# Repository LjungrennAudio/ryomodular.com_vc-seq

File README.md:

# ryomodular.com_vc-seq
 yup - here he is, he's got his own repo! it's the vc-seq!

240901254

mostly just a repo to hold the documentation relating to this module by ro modular.

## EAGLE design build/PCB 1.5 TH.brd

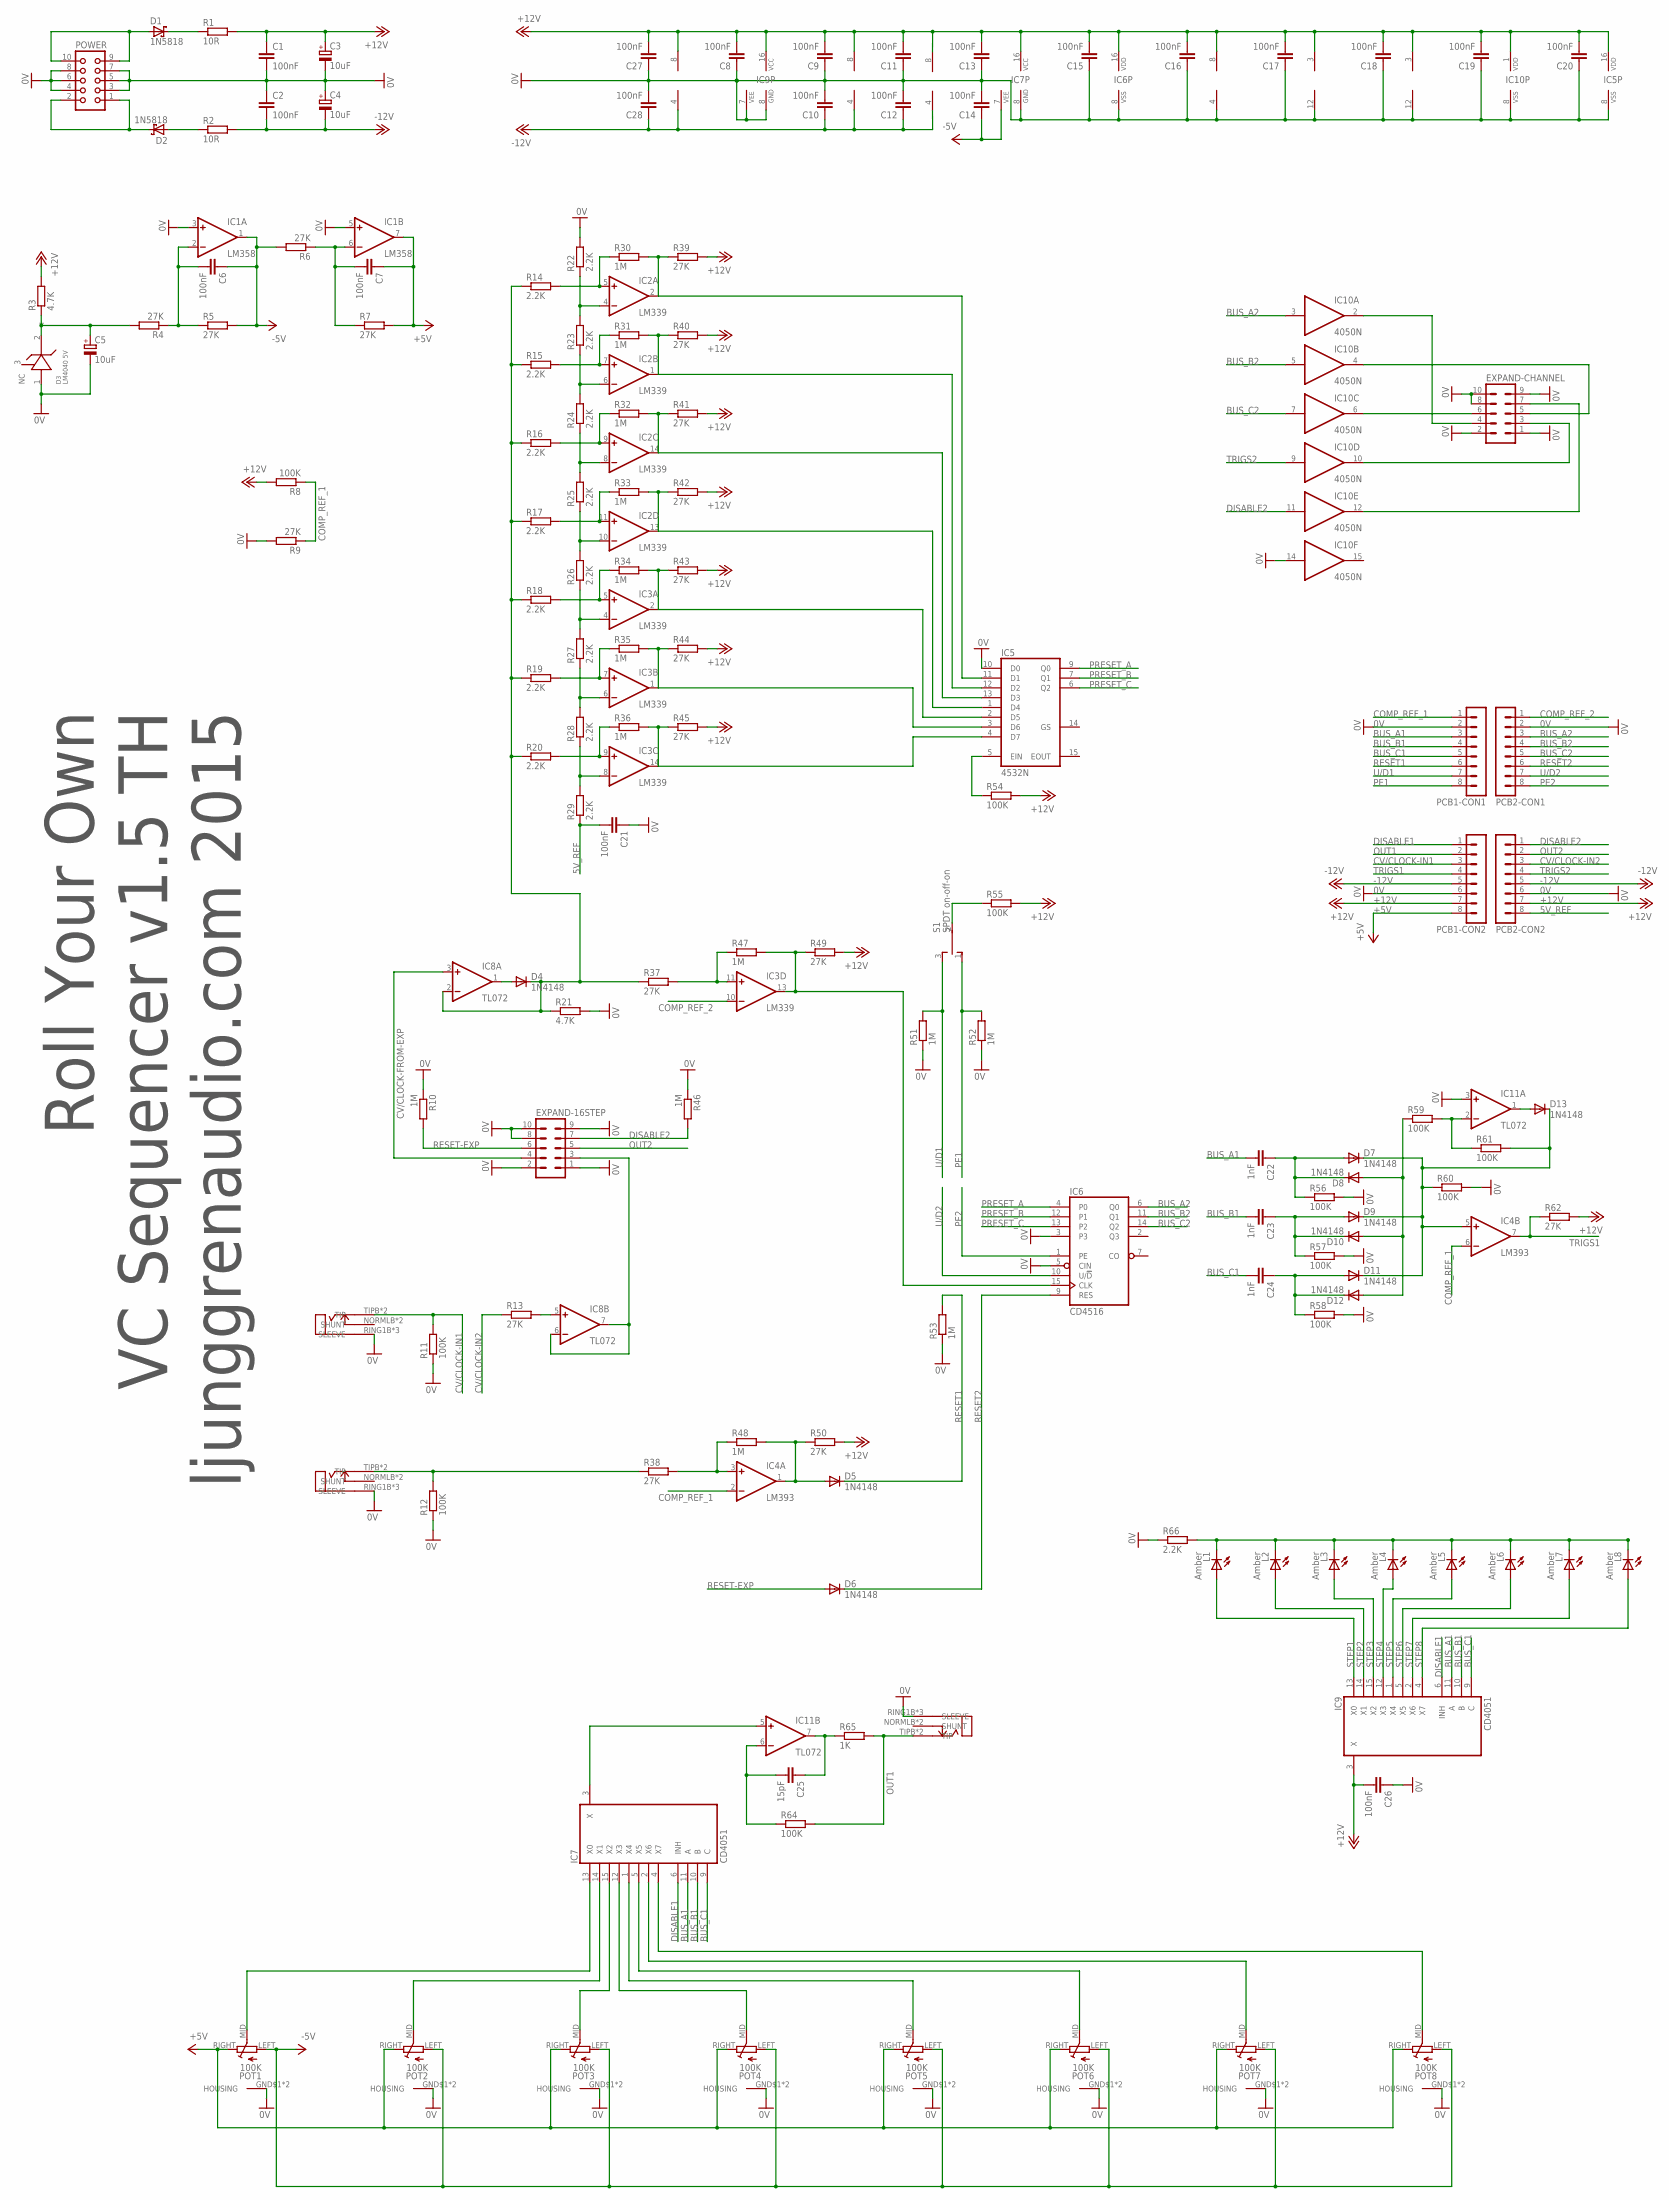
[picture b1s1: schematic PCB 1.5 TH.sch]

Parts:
C1, C2, C6, C7, C8, C9, C10, C11, C12, C13, C14, C15, C16, C17, C18, C19, C20, C21, C26, C27, C28: 100nF; C025-024X044
C3, C4, C5: 10uF; E2-5
C22, C23, C24: 1nF; C025-024X044
C25: 15pF; C025-024X044
CV/CLK-IN: ERTHENVAR_3.5MM_JACKSLOTS; ERTHENVAR-SLOTS
D1, D2: 1N5818; DO41-7
D3: LM4040 5V; TO92-LINE
D4, D5, D6, D7, D8, D9, D10, D11, D12, D13: 1N4148; DO35-6
EXPAND-16STEP: MA05-2
EXPAND-CHANNEL: MA05-2
IC1: LM358; DIL08
IC2, IC3: LM339; DIL14
IC4: LM393; DIL08
IC5: 4532N; DIL16
IC6: CD4516; DIL16
IC7, IC9: CD4051; DIL16
IC8, IC11: TL072; DIL08
IC10: 4050N; DIL16
L1, L2, L3, L4, L5, L6, L7, L8: Amber; LED3MM
OUT: ERTHENVAR_3.5MM_JACKSLOTS; ERTHENVAR-SLOTS
PCB1-CON1, PCB1-CON2, PCB2-CON1, PCB2-CON2: MA08-1
POT1, POT2, POT3, POT4, POT5, POT6, POT7, POT8: 100K; POT-ALPHA9
POWER: CON10L
R1, R2: 10R; 0207/9
R3, R21: 4.7K; 0207/9
R4, R5, R6, R7, R9, R13, R37, R38, R39, R40, R41, R42, R43, R44, R45, R49, R50, R62: 27K; 0207/9
R8, R11, R12, R54, R55, R56, R57, R58, R59, R60, R61, R64: 100K; 0207/9
R10, R30, R31, R32, R33, R34, R35, R36, R46, R47, R48, R51, R52, R53: 1M; 0207/9
R14, R15, R16, R17, R18, R19, R20, R22, R23, R24, R25, R26, R27, R28, R29, R66: 2.2K; 0207/9
R65: 1K; 0207/9
R-IN: ERTHENVAR_3.5MM_JACKSLOTS; ERTHENVAR-SLOTS
S1: SPDT on-off-on; SPDT-HORIZONTAL-TOP-SUBMINI-MULTICOMP

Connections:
0V: C1.2, C2.1, C3.-, C4.+, C5.-, C8.1, C9.1, C10.2, C11.1, C12.2, C13.1, C14.2, C15.1, C16.1, C17.1, C18.1, C19.1, C20.1, C21.1, C26.1, C27.1, C28.2, CV/CLK-IN.RING1B (SLEEVE), CV/CLK-IN.RING1T (SLEEVE), CV/CLK-IN.RING2H (SLEEVE), D3.1 (-), EXPAND-16STEP.1, EXPAND-16STEP.2, EXPAND-16STEP.8, EXPAND-16STEP.9, EXPAND-16STEP.10, EXPAND-CHANNEL.1, EXPAND-CHANNEL.2, EXPAND-CHANNEL.8, EXPAND-CHANNEL.9, EXPAND-CHANNEL.10, IC1.3 (+IN), IC1.5 (+IN), IC2.12 (V-), IC3.12 (V-), IC4.4 (V-), IC5.8 (VSS), IC5.10 (D0), IC6.3, IC6.5 (CIN), IC6.8 (VSS), IC7.8 (GND), IC9.7 (VEE), IC9.8 (GND), IC10.8 (VSS), IC10.14 (I), IC11.3 (+IN), OUT.RING1B (SLEEVE), OUT.RING1T (SLEEVE), OUT.RING2H (SLEEVE), PCB1-CON1.2, PCB1-CON2.6, PCB2-CON1.2, PCB2-CON2.6, POT1.GND$1 (HOUSING), POT1.GND$2 (HOUSING), POT2.GND$1 (HOUSING), POT2.GND$2 (HOUSING), POT3.GND$1 (HOUSING), POT3.GND$2 (HOUSING), POT4.GND$1 (HOUSING), POT4.GND$2 (HOUSING), POT5.GND$1 (HOUSING), POT5.GND$2 (HOUSING), POT6.GND$1 (HOUSING), POT6.GND$2 (HOUSING), POT7.GND$1 (HOUSING), POT7.GND$2 (HOUSING), POT8.GND$1 (HOUSING), POT8.GND$2 (HOUSING), POWER.3, POWER.4, POWER.5, POWER.6, POWER.7, POWER.8, R9.2, R10.1, R11.1, R12.1, R21.2, R22.2, R46.1, R51.1, R52.1, R53.1, R56.2, R57.2, R58.2, R60.2, R66.1, R-IN.RING1B (SLEEVE), R-IN.RING1T (SLEEVE), R-IN.RING2H (SLEEVE)
5V_REF: C21.2, PCB2-CON2.8, R29.1
+5V: C7.1, IC1.7 (OUT), PCB1-CON2.8, POT1.RIGHT, POT2.RIGHT, POT3.RIGHT, POT4.RIGHT, POT5.RIGHT, POT6.RIGHT, POT7.RIGHT, POT8.RIGHT, R7.2
+12V: C1.1, C3.+, C8.2, C9.2, C11.2, C13.2, C15.2, C16.2, C17.2, C18.2, C19.2, C20.2, C26.2, C27.2, IC1.8 (V+), IC2.3 (V+), IC3.3 (V+), IC4.8 (V+), IC5.16 (VDD), IC6.16 (VDD), IC7.16 (VCC), IC8.8 (V+), IC9.3 (X), IC9.16 (VCC), IC10.1 (VDD), IC11.8 (V+), PCB1-CON2.7, PCB2-CON2.7, R1.2, R3.2, R8.2, R39.2, R40.2, R41.2, R42.2, R43.2, R44.2, R45.2, R49.2, R50.2, R54.2, R55.2, R62.2
-5V: C6.1, C14.1, IC1.1 (OUT), IC7.7 (VEE), POT1.LEFT, POT2.LEFT, POT3.LEFT, POT4.LEFT, POT5.LEFT, POT6.LEFT, POT7.LEFT, POT8.LEFT, R5.2, R6.2
-12V: C2.2, C4.-, C10.1, C12.1, C28.1, IC1.4 (V-), IC8.4 (V-), IC11.4 (V-), PCB1-CON2.5, PCB2-CON2.5, R2.2
BUS_A1: C22.2, IC7.11 (A), IC9.11 (A), PCB1-CON1.3
BUS_A2: IC6.6 (Q0), IC10.3 (I), PCB2-CON1.3
BUS_B1: C23.2, IC7.10 (B), IC9.10 (B), PCB1-CON1.4
BUS_B2: IC6.11 (Q1), IC10.5 (I), PCB2-CON1.4
BUS_C1: C24.2, IC7.9 (C), IC9.9 (C), PCB1-CON1.5
BUS_C2: IC6.14 (Q2), IC10.7 (I), PCB2-CON1.5
COMP_REF_1: IC4.2 (-IN), IC4.6 (-IN), PCB1-CON1.1, R8.1, R9.1
COMP_REF_2: IC3.10 (-IN), PCB2-CON1.1
CV/CLK-IN: EXPAND-16STEP.3, IC8.6 (-IN), IC8.7 (OUT)
CV/CLOCK-FROM-EXP: EXPAND-16STEP.4, IC8.3 (+IN)
CV/CLOCK-IN1: CV/CLK-IN.TIPB (TIP), CV/CLK-IN.TIPT (TIP), PCB1-CON2.3, R11.2
CV/CLOCK-IN2: PCB2-CON2.3, R13.1
DISABLE1: IC7.6 (INH), IC9.6 (INH), PCB1-CON2.1
DISABLE2: EXPAND-16STEP.7, IC10.11 (I), PCB2-CON2.1, R46.2
unnamed: D4.CATHODE (C), IC8.2 (-IN), R14.1, R15.1, R16.1, R17.1, R18.1, R19.1, R20.1, R21.1, R37.1
unnamed: C25.2, IC11.6 (-IN), R64.1
unnamed: R12.2, R38.1, R-IN.TIPB (TIP), R-IN.TIPT (TIP)
unnamed: D4.ANODE (A), IC8.1 (OUT)
unnamed: C7.2, IC1.6 (-IN), R6.1, R7.1
unnamed: IC8.5 (+IN), R13.2
unnamed: IC3.11 (+IN), R37.2, R47.1
unnamed: D8.ANODE (A), D10.ANODE (A), D12.ANODE (A), R59.1
unnamed: IC4.3 (+IN), R38.2, R48.1
unnamed: IC5.5 (EIN), R54.1
unnamed: D5.ANODE (A), IC4.1 (OUT), R48.2, R50.1
unnamed: L1.K (C), L2.K (C), L3.K (C), L4.K (C), L5.K (C), L6.K (C), L7.K (C), L8.K (C), R66.2
unnamed: IC2.2 (OUT), IC5.11 (D1), R30.2, R39.1
unnamed: IC3.13 (OUT), IC6.15 (CLK), R47.2, R49.1
unnamed: IC7.4 (X7), POT8.MID
unnamed: IC7.2 (X6), POT7.MID
unnamed: IC7.5 (X5), POT6.MID
unnamed: IC7.1 (X4), POT5.MID
unnamed: IC7.12 (X3), POT4.MID
unnamed: IC7.15 (X2), POT3.MID
unnamed: IC7.14 (X1), POT2.MID
unnamed: IC7.13 (X0), POT1.MID
unnamed: IC2.5 (+IN), R14.2, R30.1
unnamed: D1.A, POWER.9, POWER.10
unnamed: D1.C, R1.1
unnamed: D2.A, R2.1
unnamed: R55.1, S1.2
unnamed: C6.2, IC1.2 (-IN), R4.1, R5.1
unnamed: D2.C, POWER.1, POWER.2
unnamed: IC2.4 (-IN), R22.1, R23.2
unnamed: IC2.1 (OUT), IC5.12 (D2), R31.2, R40.1
unnamed: IC2.7 (+IN), R15.2, R31.1
unnamed: IC2.6 (-IN), R23.1, R24.2
unnamed: C5.+, D3.2 (+), R3.1, R4.2
unnamed: IC2.14 (OUT), IC5.13 (D3), R32.2, R41.1
unnamed: IC2.9 (+IN), R16.2, R32.1
unnamed: IC7.3 (X), IC11.5 (+IN)
unnamed: C22.1, D7.ANODE (A), D8.CATHODE (C), R56.1
unnamed: IC2.8 (-IN), R24.1, R25.2
unnamed: IC2.13 (OUT), IC5.1 (D4), R33.2, R42.1
unnamed: IC2.11 (+IN), R17.2, R33.1
unnamed: IC2.10 (-IN), R25.1, R26.2
unnamed: C23.1, D9.ANODE (A), D10.CATHODE (C), R57.1
unnamed: IC3.2 (OUT), IC5.2 (D5), R34.2, R43.1
unnamed: IC3.5 (+IN), R18.2, R34.1
unnamed: IC3.4 (-IN), R26.1, R27.2
unnamed: C24.1, D11.ANODE (A), D12.CATHODE (C), R58.1
unnamed: IC3.1 (OUT), IC5.3 (D6), R35.2, R44.1
unnamed: IC3.7 (+IN), R19.2, R35.1
unnamed: D13.ANODE (A), IC11.1 (OUT)
unnamed: IC3.6 (-IN), R27.1, R28.2
unnamed: IC3.14 (OUT), IC5.4 (D7), R36.2, R45.1
unnamed: IC3.9 (+IN), R20.2, R36.1
unnamed: IC3.8 (-IN), R28.1, R29.2
unnamed: IC11.2 (-IN), R59.2, R61.1
unnamed: D7.CATHODE (C), D9.CATHODE (C), D11.CATHODE (C), D13.CATHODE (C), IC4.5 (+IN), R60.1, R61.2
unnamed: EXPAND-CHANNEL.4, IC10.2 (O)
unnamed: EXPAND-CHANNEL.6, IC10.6 (O)
unnamed: EXPAND-CHANNEL.5, IC10.4 (O)
unnamed: EXPAND-CHANNEL.3, IC10.10 (O)
unnamed: EXPAND-CHANNEL.7, IC10.12 (O)
unnamed: C25.1, IC11.7 (OUT), R65.1
OUT1: OUT.TIPB (TIP), OUT.TIPT (TIP), PCB1-CON2.2, R64.2, R65.2
OUT2: EXPAND-16STEP.5, PCB2-CON2.2
PE1: PCB1-CON1.8, R52.2, S1.1
PE2: IC6.1 (PE), PCB2-CON1.8
PRESET_A: IC5.9 (Q0), IC6.4 (P0)
PRESET_B: IC5.7 (Q1), IC6.12 (P1)
PRESET_C: IC5.6 (Q2), IC6.13 (P2)
RESET1: D5.CATHODE (C), PCB1-CON1.6, R53.2
RESET2: D6.CATHODE (C), IC6.9 (RES), PCB2-CON1.6
RESET-EXP: D6.ANODE (A), EXPAND-16STEP.6, R10.2
STEP1: IC9.13 (X0), L1.A
STEP2: IC9.14 (X1), L2.A
STEP3: IC9.15 (X2), L3.A
STEP4: IC9.12 (X3), L4.A
STEP5: IC9.1 (X4), L5.A
STEP6: IC9.5 (X5), L6.A
STEP7: IC9.2 (X6), L7.A
STEP8: IC9.4 (X7), L8.A
TRIGS1: IC4.7 (OUT), PCB1-CON2.4, R62.1
TRIGS2: IC10.9 (I), PCB2-CON2.4
U/D1: PCB1-CON1.7, R51.2, S1.3
U/D2: IC6.10 (U/!D), PCB2-CON1.7

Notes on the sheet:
Roll Your Own VC Sequencer v1.5 TH ljunggrenaudio.com 2015

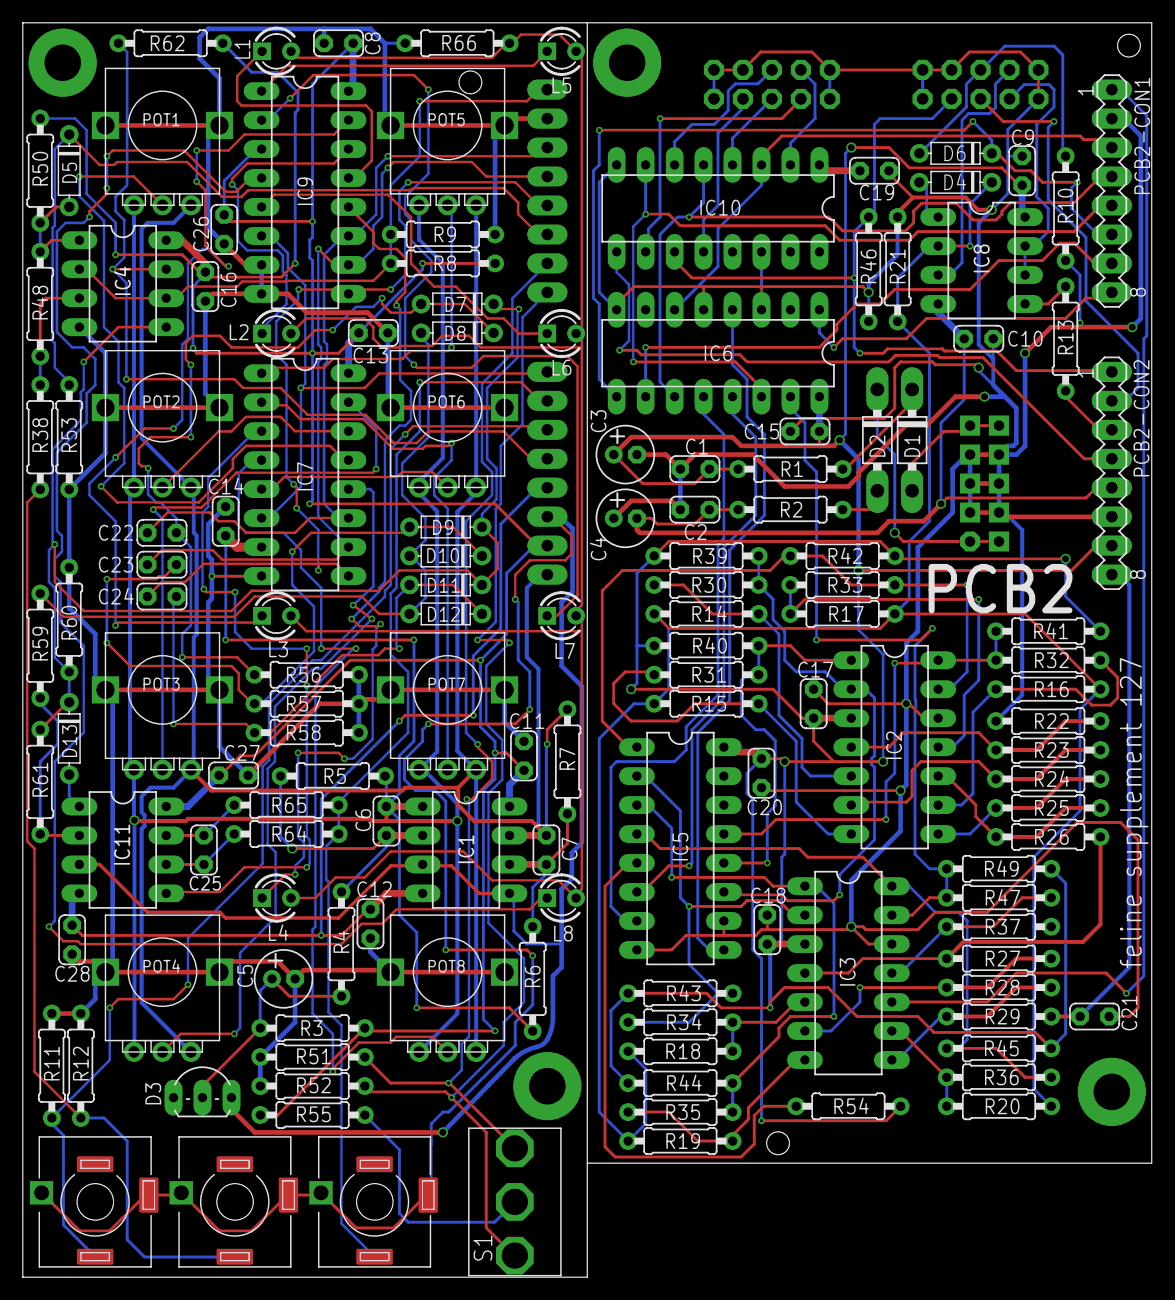
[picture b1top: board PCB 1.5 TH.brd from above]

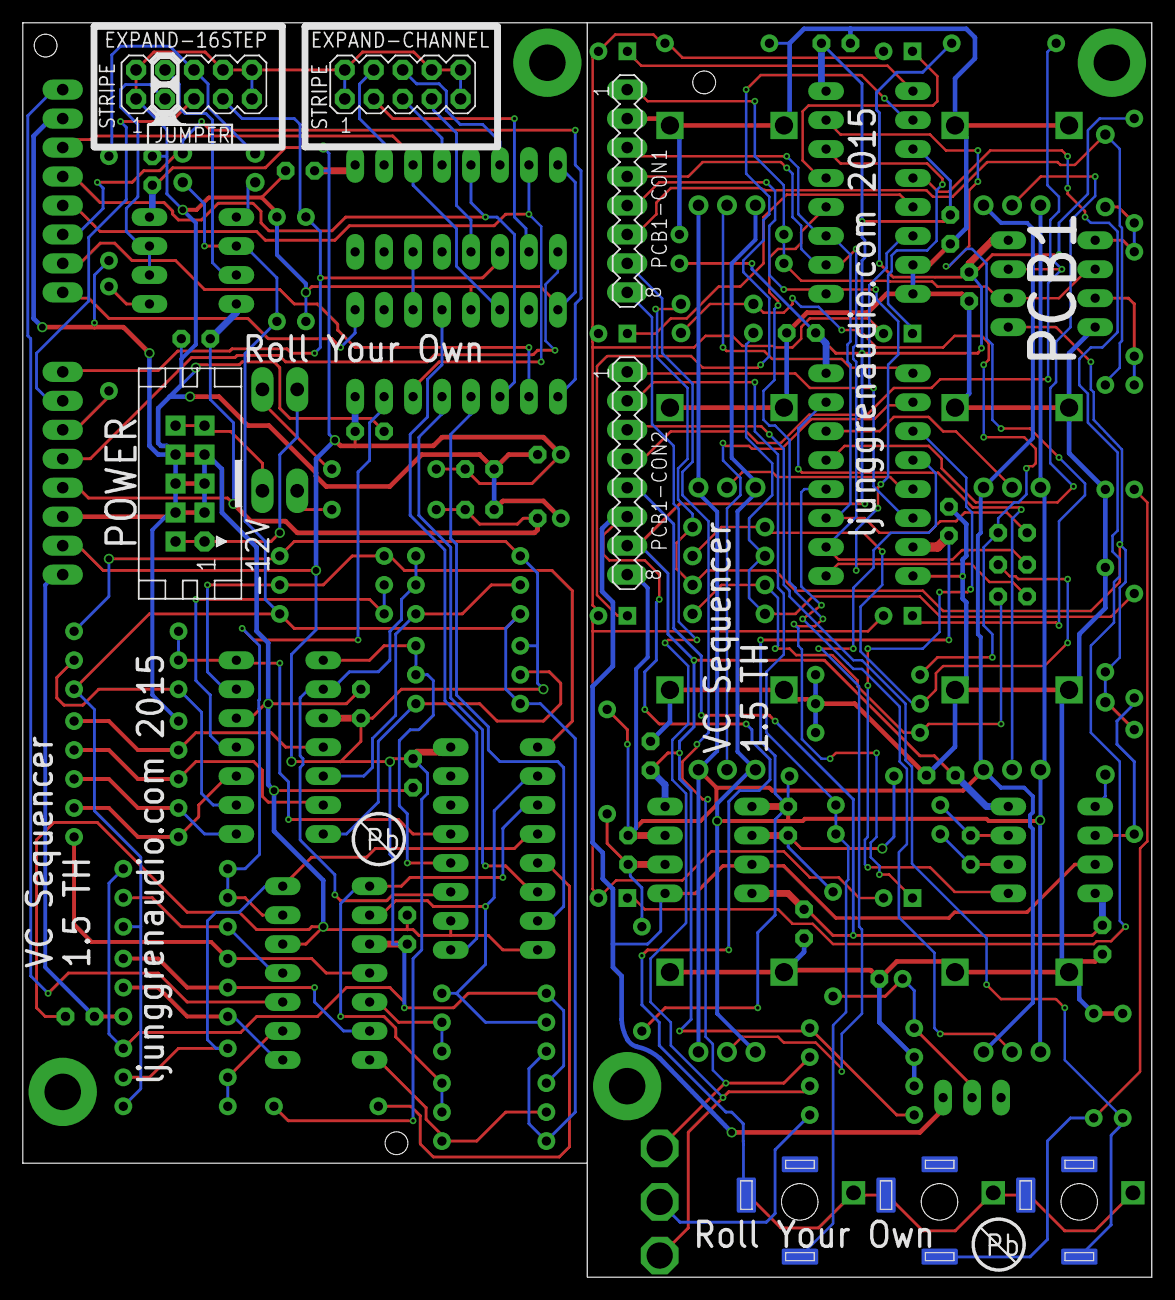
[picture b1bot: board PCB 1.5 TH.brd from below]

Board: 2 copper layers, 99.0 x 110.0 mm, 144 parts (5 on the bottom side), 104 nets.

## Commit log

2024-08-31 init commit for vc-seq
    yup, it's now avail for all!
2024-09-06 updated the readme
2025-01-13 filing
